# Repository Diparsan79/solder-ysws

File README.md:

# solder-ysws

The main function of this PCB is that it looks ilke a some kinda kitty but its irregular in shape lowk , and it runs on a CR2032 battery 
## Schematic

## PCB

## How to build
place the parts according to schematic and solder them; EZZZZ
## BOM
- 1 	Battery
- 5   LED
- 5	  470 Resistor

Made by flameX!!

Made as a part of http://solder.hackclub.com/!

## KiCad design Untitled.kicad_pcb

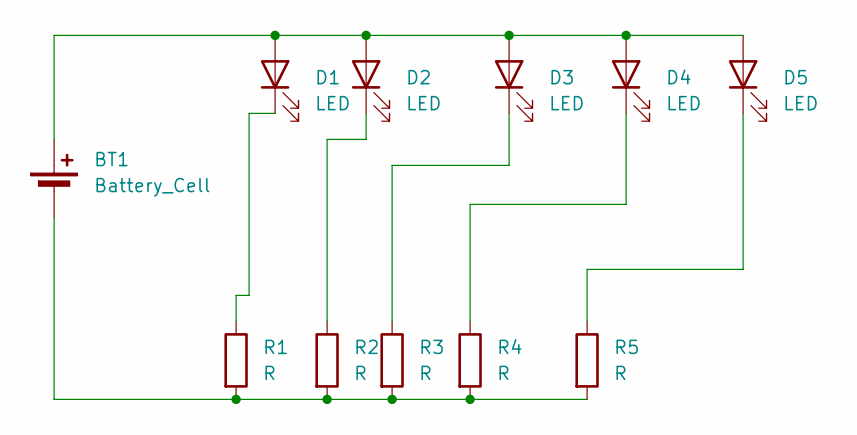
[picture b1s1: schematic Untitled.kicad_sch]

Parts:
BT1: Battery_Cell; BatteryHolder_Keystone_3034_1x20mm
D1, D2, D3, D4, D5: LED; LED_D5.0mm
R1, R2, R3, R4, R5: R; R_Axial_DIN0207_L6.3mm_D2.5mm_P7.62mm_Horizontal

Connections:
unnamed: BT1.1 (+), D1.2 (A), D2.2 (A), D3.2 (A), D4.2 (A), D5.2 (A)
unnamed: BT1.2 (-), R1.2, R2.2, R3.2, R4.2, R5.2
unnamed: D1.1 (K), R1.1
unnamed: D2.1 (K), R2.1
unnamed: D3.1 (K), R3.1
unnamed: D4.1 (K), R4.1
unnamed: D5.1 (K), R5.1

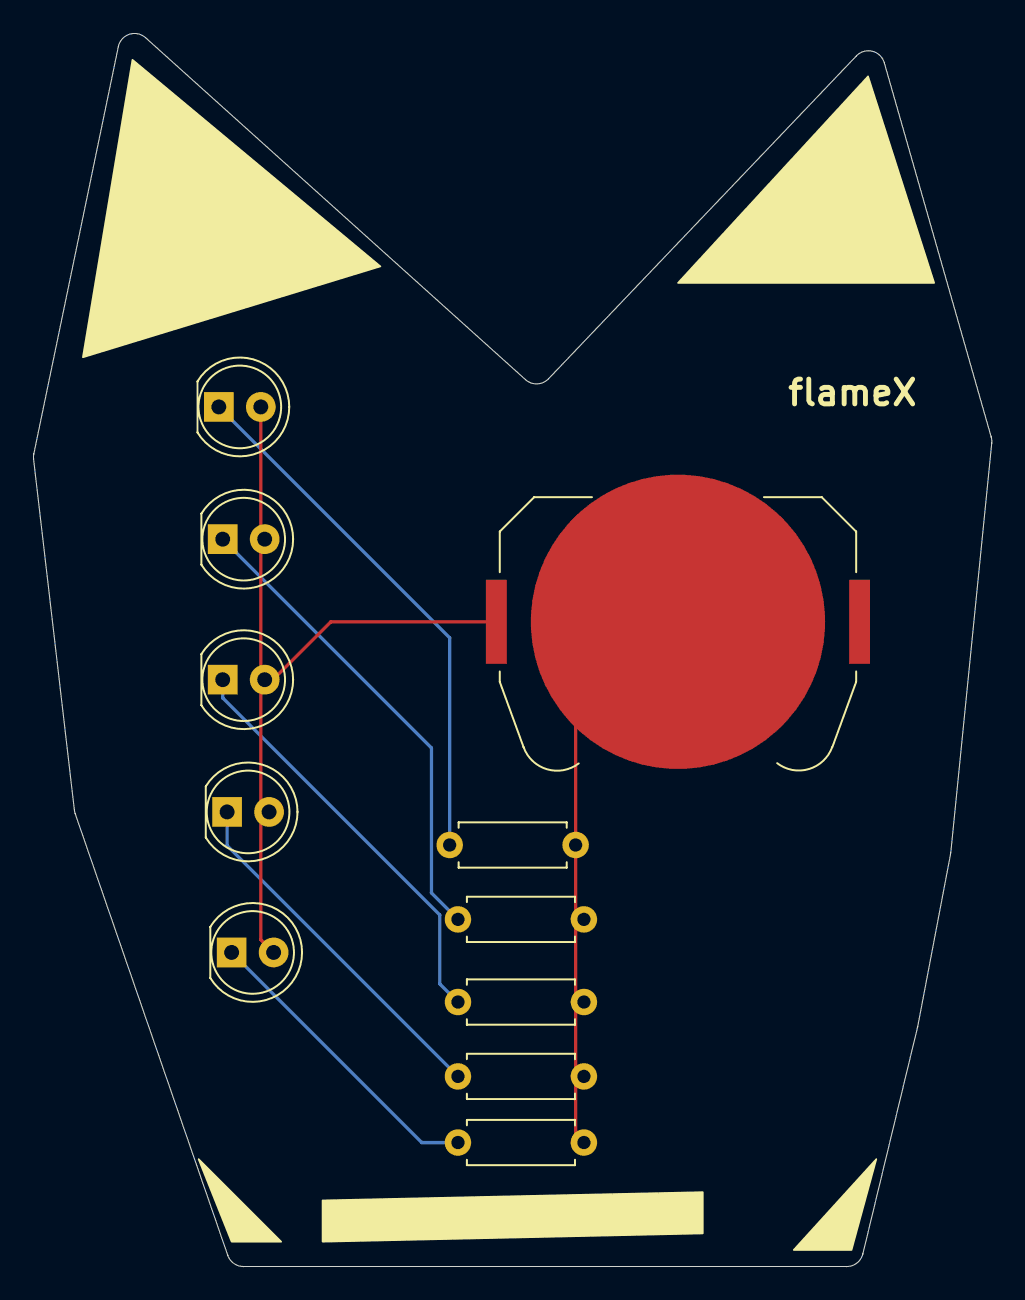
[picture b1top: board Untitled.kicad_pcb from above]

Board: 2 copper layers, 58.0 x 74.6 mm, 11 parts (0 on the bottom side), 7 nets.
